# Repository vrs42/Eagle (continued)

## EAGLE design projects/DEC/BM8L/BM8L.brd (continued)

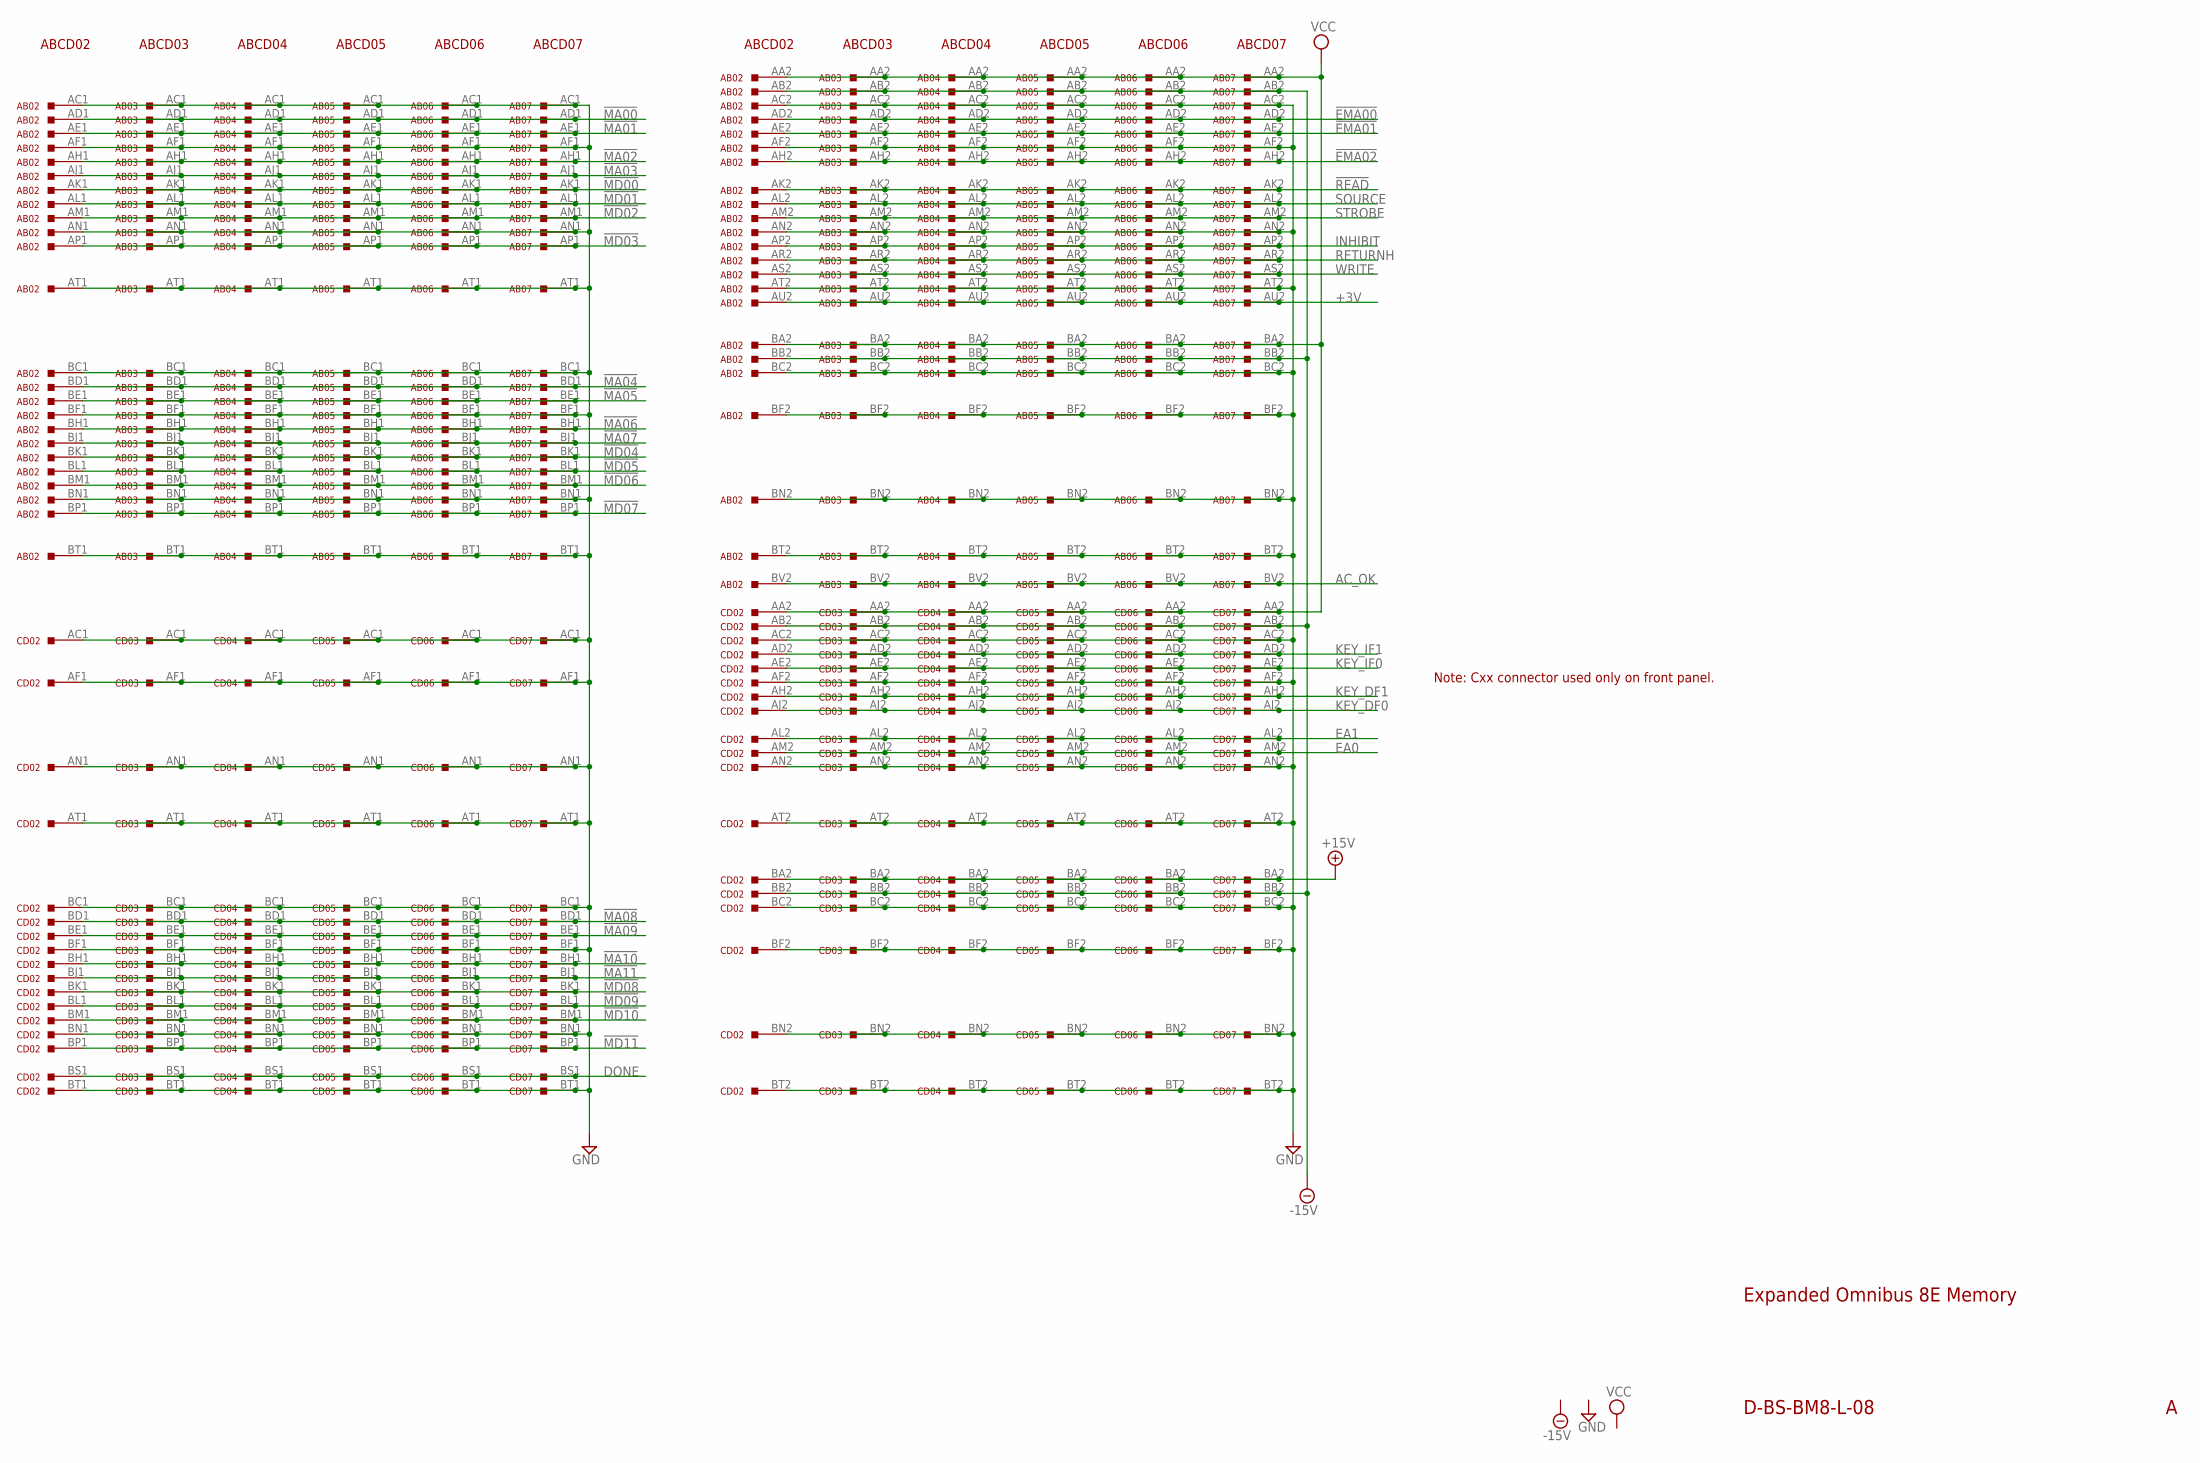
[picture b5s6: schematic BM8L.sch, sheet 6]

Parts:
AB02, AB03, AB04, AB05, AB06: M935; H807-2
AB07: M849; H807-2
CD02, CD03, CD04, CD05, CD06: M935; H807-2
CD07: M849; H807-2

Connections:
!EMA00: AB02.AD2, AB03.AD2, AB04.AD2, AB05.AD2, AB06.AD2, AB07.AD2; also elsewhere on the board
!EMA01: AB02.AE2, AB03.AE2, AB04.AE2, AB05.AE2, AB06.AE2, AB07.AE2; also elsewhere on the board
!EMA02: AB02.AH2, AB03.AH2, AB04.AH2, AB05.AH2, AB06.AH2, AB07.AH2; also elsewhere on the board
!MA00: AB02.AD1, AB03.AD1, AB04.AD1, AB05.AD1, AB06.AD1, AB07.AD1; also elsewhere on the board
!MA01: AB02.AE1, AB03.AE1, AB04.AE1, AB05.AE1, AB06.AE1, AB07.AE1; also elsewhere on the board
!MA02: AB02.AH1, AB03.AH1, AB04.AH1, AB05.AH1, AB06.AH1, AB07.AH1; also elsewhere on the board
!MA03: AB02.AJ1, AB03.AJ1, AB04.AJ1, AB05.AJ1, AB06.AJ1, AB07.AJ1; also elsewhere on the board
!MA04: AB02.BD1, AB03.BD1, AB04.BD1, AB05.BD1, AB06.BD1, AB07.BD1; also elsewhere on the board
!MA05: AB02.BE1, AB03.BE1, AB04.BE1, AB05.BE1, AB06.BE1, AB07.BE1; also elsewhere on the board
!MA06: AB02.BH1, AB03.BH1, AB04.BH1, AB05.BH1, AB06.BH1, AB07.BH1; also elsewhere on the board
!MA07: AB02.BJ1, AB03.BJ1, AB04.BJ1, AB05.BJ1, AB06.BJ1, AB07.BJ1; also elsewhere on the board
!MA08: CD02.BD1, CD03.BD1, CD04.BD1, CD05.BD1, CD06.BD1, CD07.BD1; also elsewhere on the board
!MA09: CD02.BE1, CD03.BE1, CD04.BE1, CD05.BE1, CD06.BE1, CD07.BE1; also elsewhere on the board
!MA10: CD02.BH1, CD03.BH1, CD04.BH1, CD05.BH1, CD06.BH1, CD07.BH1; also elsewhere on the board
!MA11: CD02.BJ1, CD03.BJ1, CD04.BJ1, CD05.BJ1, CD06.BJ1, CD07.BJ1; also elsewhere on the board
!MD00: AB02.AK1, AB03.AK1, AB04.AK1, AB05.AK1, AB06.AK1, AB07.AK1
!MD01: AB02.AL1, AB03.AL1, AB04.AL1, AB05.AL1, AB06.AL1, AB07.AL1
!MD02: AB02.AM1, AB03.AM1, AB04.AM1, AB05.AM1, AB06.AM1, AB07.AM1
!MD03: AB02.AP1, AB03.AP1, AB04.AP1, AB05.AP1, AB06.AP1, AB07.AP1
!MD04: AB02.BK1, AB03.BK1, AB04.BK1, AB05.BK1, AB06.BK1, AB07.BK1
!MD05: AB02.BL1, AB03.BL1, AB04.BL1, AB05.BL1, AB06.BL1, AB07.BL1
!MD06: AB02.BM1, AB03.BM1, AB04.BM1, AB05.BM1, AB06.BM1, AB07.BM1
!MD07: AB02.BP1, AB03.BP1, AB04.BP1, AB05.BP1, AB06.BP1, AB07.BP1
!MD08: CD02.BK1, CD03.BK1, CD04.BK1, CD05.BK1, CD06.BK1, CD07.BK1
!MD09: CD02.BL1, CD03.BL1, CD04.BL1, CD05.BL1, CD06.BL1, CD07.BL1
!MD10: CD02.BM1, CD03.BM1, CD04.BM1, CD05.BM1, CD06.BM1, CD07.BM1
!MD11: CD02.BP1, CD03.BP1, CD04.BP1, CD05.BP1, CD06.BP1, CD07.BP1
!READ: AB02.AK2, AB03.AK2, AB04.AK2, AB05.AK2, AB06.AK2, AB07.AK2; also elsewhere on the board
+3V: AB02.AU2, AB03.AU2, AB04.AU2, AB05.AU2, AB06.AU2, AB07.AU2
+15V: CD02.BA2, CD03.BA2, CD04.BA2, CD05.BA2, CD06.BA2, CD07.BA2
-15V: AB02.AB2, AB02.BB2, AB03.AB2, AB03.BB2, AB04.AB2, AB04.BB2, AB05.AB2, AB05.BB2, AB06.AB2, AB06.BB2, AB07.AB2, AB07.BB2, CD02.AB2, CD02.BB2, CD03.AB2, CD03.BB2, CD04.AB2, CD04.BB2, CD05.AB2, CD05.BB2, CD06.AB2, CD06.BB2, CD07.AB2, CD07.BB2; also elsewhere on the board
AC_OK: AB02.BV2, AB03.BV2, AB04.BV2, AB05.BV2, AB06.BV2, AB07.BV2
DONE: CD02.BS1, CD03.BS1, CD04.BS1, CD05.BS1, CD06.BS1, CD07.BS1; also elsewhere on the board
EA0: CD02.AM2, CD03.AM2, CD04.AM2, CD05.AM2, CD06.AM2, CD07.AM2; also elsewhere on the board
EA1: CD02.AL2, CD03.AL2, CD04.AL2, CD05.AL2, CD06.AL2, CD07.AL2; also elsewhere on the board
GND: AB02.AC1, AB02.AC2, AB02.AF1, AB02.AF2, AB02.AN1, AB02.AN2, AB02.AT1, AB02.AT2, AB02.BC1, AB02.BC2, AB02.BF1, AB02.BF2, AB02.BN1, AB02.BN2, AB02.BT1, AB02.BT2, AB03.AC1, AB03.AC2, AB03.AF1, AB03.AF2, AB03.AN1, AB03.AN2, AB03.AT1, AB03.AT2, AB03.BC1, AB03.BC2, AB03.BF1, AB03.BF2, AB03.BN1, AB03.BN2, AB03.BT1, AB03.BT2, AB04.AC1, AB04.AC2, AB04.AF1, AB04.AF2, AB04.AN1, AB04.AN2, AB04.AT1, AB04.AT2, AB04.BC1, AB04.BC2, AB04.BF1, AB04.BF2, AB04.BN1, AB04.BN2, AB04.BT1, AB04.BT2, AB05.AC1, AB05.AC2, AB05.AF1, AB05.AF2, AB05.AN1, AB05.AN2, AB05.AT1, AB05.AT2, AB05.BC1, AB05.BC2, AB05.BF1, AB05.BF2, AB05.BN1, AB05.BN2, AB05.BT1, AB05.BT2, AB06.AC1, AB06.AC2, AB06.AF1, AB06.AF2, AB06.AN1, AB06.AN2, AB06.AT1, AB06.AT2, AB06.BC1, AB06.BC2, AB06.BF1, AB06.BF2, AB06.BN1, AB06.BN2, AB06.BT1, AB06.BT2, AB07.AC1, AB07.AC2, AB07.AF1, AB07.AF2, AB07.AN1, AB07.AN2, AB07.AT1, AB07.AT2, AB07.BC1, AB07.BC2, AB07.BF1, AB07.BF2, AB07.BN1, AB07.BN2, AB07.BT1, AB07.BT2, CD02.AC1, CD02.AC2, CD02.AF1, CD02.AF2, CD02.AN1, CD02.AN2, CD02.AT1, CD02.AT2, CD02.BC1, CD02.BC2, CD02.BF1, CD02.BF2, CD02.BN1, CD02.BN2, CD02.BT1, CD02.BT2, CD03.AC1, CD03.AC2, CD03.AF1, CD03.AF2, CD03.AN1, CD03.AN2, CD03.AT1, CD03.AT2, CD03.BC1, CD03.BC2, CD03.BF1, CD03.BF2, CD03.BN1, CD03.BN2, CD03.BT1, CD03.BT2, CD04.AC1, CD04.AC2, CD04.AF1, CD04.AF2, CD04.AN1, CD04.AN2, CD04.AT1, CD04.AT2, CD04.BC1, CD04.BC2, CD04.BF1, CD04.BF2, CD04.BN1, CD04.BN2, CD04.BT1, CD04.BT2, CD05.AC1, CD05.AC2, CD05.AF1, CD05.AF2, CD05.AN1, CD05.AN2, CD05.AT1, CD05.AT2, CD05.BC1, CD05.BC2, CD05.BF1, CD05.BF2, CD05.BN1, CD05.BN2, CD05.BT1, CD05.BT2, CD06.AC1, CD06.AC2, CD06.AF1, CD06.AF2, CD06.AN1, CD06.AN2, CD06.AT1, CD06.AT2, CD06.BC1, CD06.BC2, CD06.BF1, CD06.BF2, CD06.BN1, CD06.BN2, CD06.BT1, CD06.BT2, CD07.AC1, CD07.AC2, CD07.AF1, CD07.AF2, CD07.AN1, CD07.AN2, CD07.AT1, CD07.AT2, CD07.BC1, CD07.BC2, CD07.BF1, CD07.BF2, CD07.BN1, CD07.BN2, CD07.BT1, CD07.BT2; also elsewhere on the board
INHIBIT: AB02.AP2, AB03.AP2, AB04.AP2, AB05.AP2, AB06.AP2, AB07.AP2; also elsewhere on the board
KEY_DF0: CD02.AJ2, CD03.AJ2, CD04.AJ2, CD05.AJ2, CD06.AJ2, CD07.AJ2; also elsewhere on the board
KEY_DF1: CD02.AH2, CD03.AH2, CD04.AH2, CD05.AH2, CD06.AH2, CD07.AH2; also elsewhere on the board
KEY_IF0: CD02.AE2, CD03.AE2, CD04.AE2, CD05.AE2, CD06.AE2, CD07.AE2; also elsewhere on the board
KEY_IF1: CD02.AD2, CD03.AD2, CD04.AD2, CD05.AD2, CD06.AD2, CD07.AD2; also elsewhere on the board
RETURNH: AB02.AR2, AB03.AR2, AB04.AR2, AB05.AR2, AB06.AR2, AB07.AR2; also elsewhere on the board
SOURCE: AB02.AL2, AB03.AL2, AB04.AL2, AB05.AL2, AB06.AL2, AB07.AL2; also elsewhere on the board
STROBE: AB02.AM2, AB03.AM2, AB04.AM2, AB05.AM2, AB06.AM2, AB07.AM2; also elsewhere on the board
VCC: AB02.AA2, AB02.BA2, AB03.AA2, AB03.BA2, AB04.AA2, AB04.BA2, AB05.AA2, AB05.BA2, AB06.AA2, AB06.BA2, AB07.AA2, AB07.BA2, CD02.AA2, CD03.AA2, CD04.AA2, CD05.AA2, CD06.AA2, CD07.AA2; also elsewhere on the board
WRITE: AB02.AS2, AB03.AS2, AB04.AS2, AB05.AS2, AB06.AS2, AB07.AS2; also elsewhere on the board

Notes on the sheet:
D-BS-BM8-L-08
Expanded Omnibus 8E Memory
Note: Cxx connector used only on front panel.
ABCD02
ABCD03
ABCD04
ABCD05
ABCD06
ABCD07

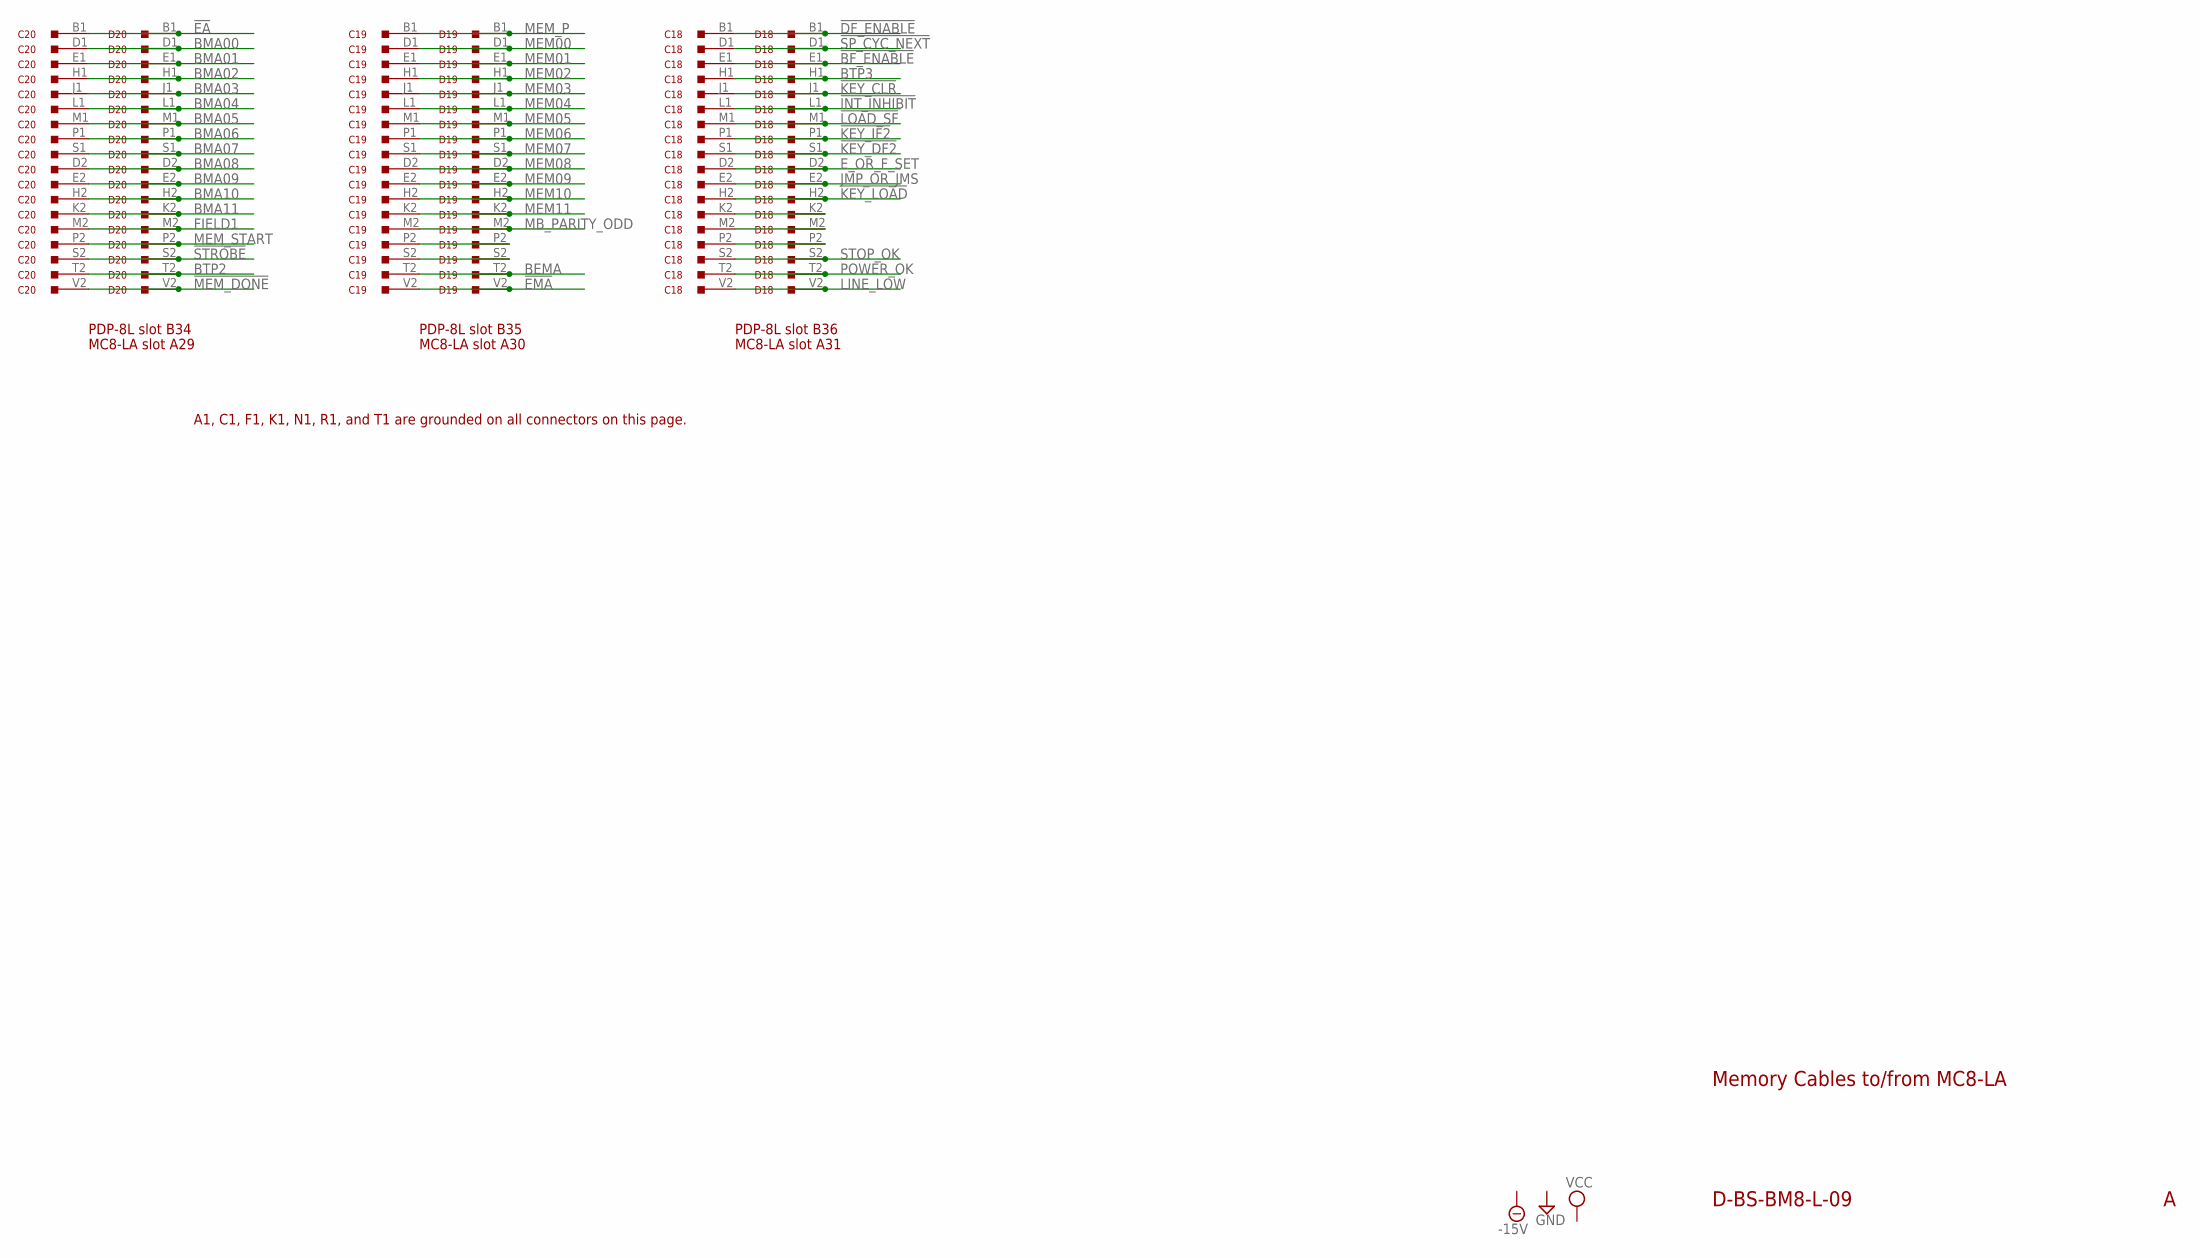
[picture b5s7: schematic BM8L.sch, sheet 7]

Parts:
C18, C19, C20: M903; H807
D18, D19, D20: M903; H807

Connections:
!BF_ENABLE: C18.E1, D18.E1; also elsewhere on the board
!DF_ENABLE: C18.B1, D18.B1; also elsewhere on the board
!EA: C20.B1, D20.B1; also elsewhere on the board
!EMA: C19.V2, D19.V2; also elsewhere on the board
!INT_INHIBIT: C18.L1, D18.L1; also elsewhere on the board
!KEY_CLR: C18.J1, D18.J1; also elsewhere on the board
!KEY_DF2: C18.S1, D18.S1; also elsewhere on the board
!KEY_IF2: C18.P1, D18.P1; also elsewhere on the board
!KEY_LOAD: C18.H2, D18.H2; also elsewhere on the board
!LOAD_SF: C18.M1, D18.M1; also elsewhere on the board
!MEM_DONE: C20.V2, D20.V2; also elsewhere on the board
!SP_CYC_NEXT: C18.D1, D18.D1; also elsewhere on the board
!STROBE: C20.S2, D20.S2; also elsewhere on the board
BEMA: C19.T2, D19.T2; also elsewhere on the board
BMA00: C20.D1, D20.D1; also elsewhere on the board
BMA01: C20.E1, D20.E1; also elsewhere on the board
BMA02: C20.H1, D20.H1; also elsewhere on the board
BMA03: C20.J1, D20.J1; also elsewhere on the board
BMA04: C20.L1, D20.L1; also elsewhere on the board
BMA05: C20.M1, D20.M1; also elsewhere on the board
BMA06: C20.P1, D20.P1; also elsewhere on the board
BMA07: C20.S1, D20.S1; also elsewhere on the board
BMA08: C20.D2, D20.D2; also elsewhere on the board
BMA09: C20.E2, D20.E2; also elsewhere on the board
BMA10: C20.H2, D20.H2; also elsewhere on the board
BMA11: C20.K2, D20.K2; also elsewhere on the board
BTP2: C20.T2, D20.T2; also elsewhere on the board
BTP3: C18.H1, D18.H1; also elsewhere on the board
E_OR_F_SET: C18.D2, D18.D2; also elsewhere on the board
FIELD1: C20.M2, D20.M2; also elsewhere on the board
GND: C18.A1 (GND), C18.C1 (GND), C18.C2 (GND), C18.F1 (GND), C18.F2 (GND), C18.J2 (GND), C18.K1 (GND), C18.L2 (GND), C18.N1 (GND), C18.N2 (GND), C18.R1 (GND), C18.R2 (GND), C18.T1 (GND), C18.U2 (GND), C19.A1 (GND), C19.C1 (GND), C19.C2 (GND), C19.F1 (GND), C19.F2 (GND), C19.J2 (GND), C19.K1 (GND), C19.L2 (GND), C19.N1 (GND), C19.N2 (GND), C19.R1 (GND), C19.R2 (GND), C19.T1 (GND), C19.U2 (GND), C20.A1 (GND), C20.C1 (GND), C20.C2 (GND), C20.F1 (GND), C20.F2 (GND), C20.J2 (GND), C20.K1 (GND), C20.L2 (GND), C20.N1 (GND), C20.N2 (GND), C20.R1 (GND), C20.R2 (GND), C20.T1 (GND), C20.U2 (GND), D18.A1 (GND), D18.C1 (GND), D18.C2 (GND), D18.F1 (GND), D18.F2 (GND), D18.J2 (GND), D18.K1 (GND), D18.L2 (GND), D18.N1 (GND), D18.N2 (GND), D18.R1 (GND), D18.R2 (GND), D18.T1 (GND), D18.U2 (GND), D19.A1 (GND), D19.C1 (GND), D19.C2 (GND), D19.F1 (GND), D19.F2 (GND), D19.J2 (GND), D19.K1 (GND), D19.L2 (GND), D19.N1 (GND), D19.N2 (GND), D19.R1 (GND), D19.R2 (GND), D19.T1 (GND), D19.U2 (GND), D20.A1 (GND), D20.C1 (GND), D20.C2 (GND), D20.F1 (GND), D20.F2 (GND), D20.J2 (GND), D20.K1 (GND), D20.L2 (GND), D20.N1 (GND), D20.N2 (GND), D20.R1 (GND), D20.R2 (GND), D20.T1 (GND), D20.U2 (GND); also elsewhere on the board
JMP_OR_JMS: C18.E2, D18.E2; also elsewhere on the board
LINE_LOW: C18.V2, D18.V2
MB_PARITY_ODD: C19.M2, D19.M2
MEM00: C19.D1, D19.D1; also elsewhere on the board
MEM01: C19.E1, D19.E1; also elsewhere on the board
MEM02: C19.H1, D19.H1; also elsewhere on the board
MEM03: C19.J1, D19.J1; also elsewhere on the board
MEM04: C19.L1, D19.L1; also elsewhere on the board
MEM05: C19.M1, D19.M1; also elsewhere on the board
MEM06: C19.P1, D19.P1; also elsewhere on the board
MEM07: C19.S1, D19.S1; also elsewhere on the board
MEM08: C19.D2, D19.D2; also elsewhere on the board
MEM09: C19.E2, D19.E2; also elsewhere on the board
MEM10: C19.H2, D19.H2; also elsewhere on the board
MEM11: C19.K2, D19.K2; also elsewhere on the board
MEM_P: C19.B1, D19.B1
MEM_START: C20.P2, D20.P2; also elsewhere on the board
unnamed: C19.P2, D19.P2
unnamed: C19.S2, D19.S2
unnamed: C18.P2, D18.P2
unnamed: C18.M2, D18.M2
unnamed: C18.K2, D18.K2
POWER_OK: C18.T2, D18.T2; also elsewhere on the board
STOP_OK: C18.S2, D18.S2

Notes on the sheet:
D-BS-BM8-L-09
Memory Cables to/from MC8-LA
A1, C1, F1, K1, N1, R1, and T1 are grounded on all connectors on this page.
PDP-8L slot B34
MC8-LA slot A29
PDP-8L slot B35
MC8-LA slot A30
PDP-8L slot B36
MC8-LA slot A31

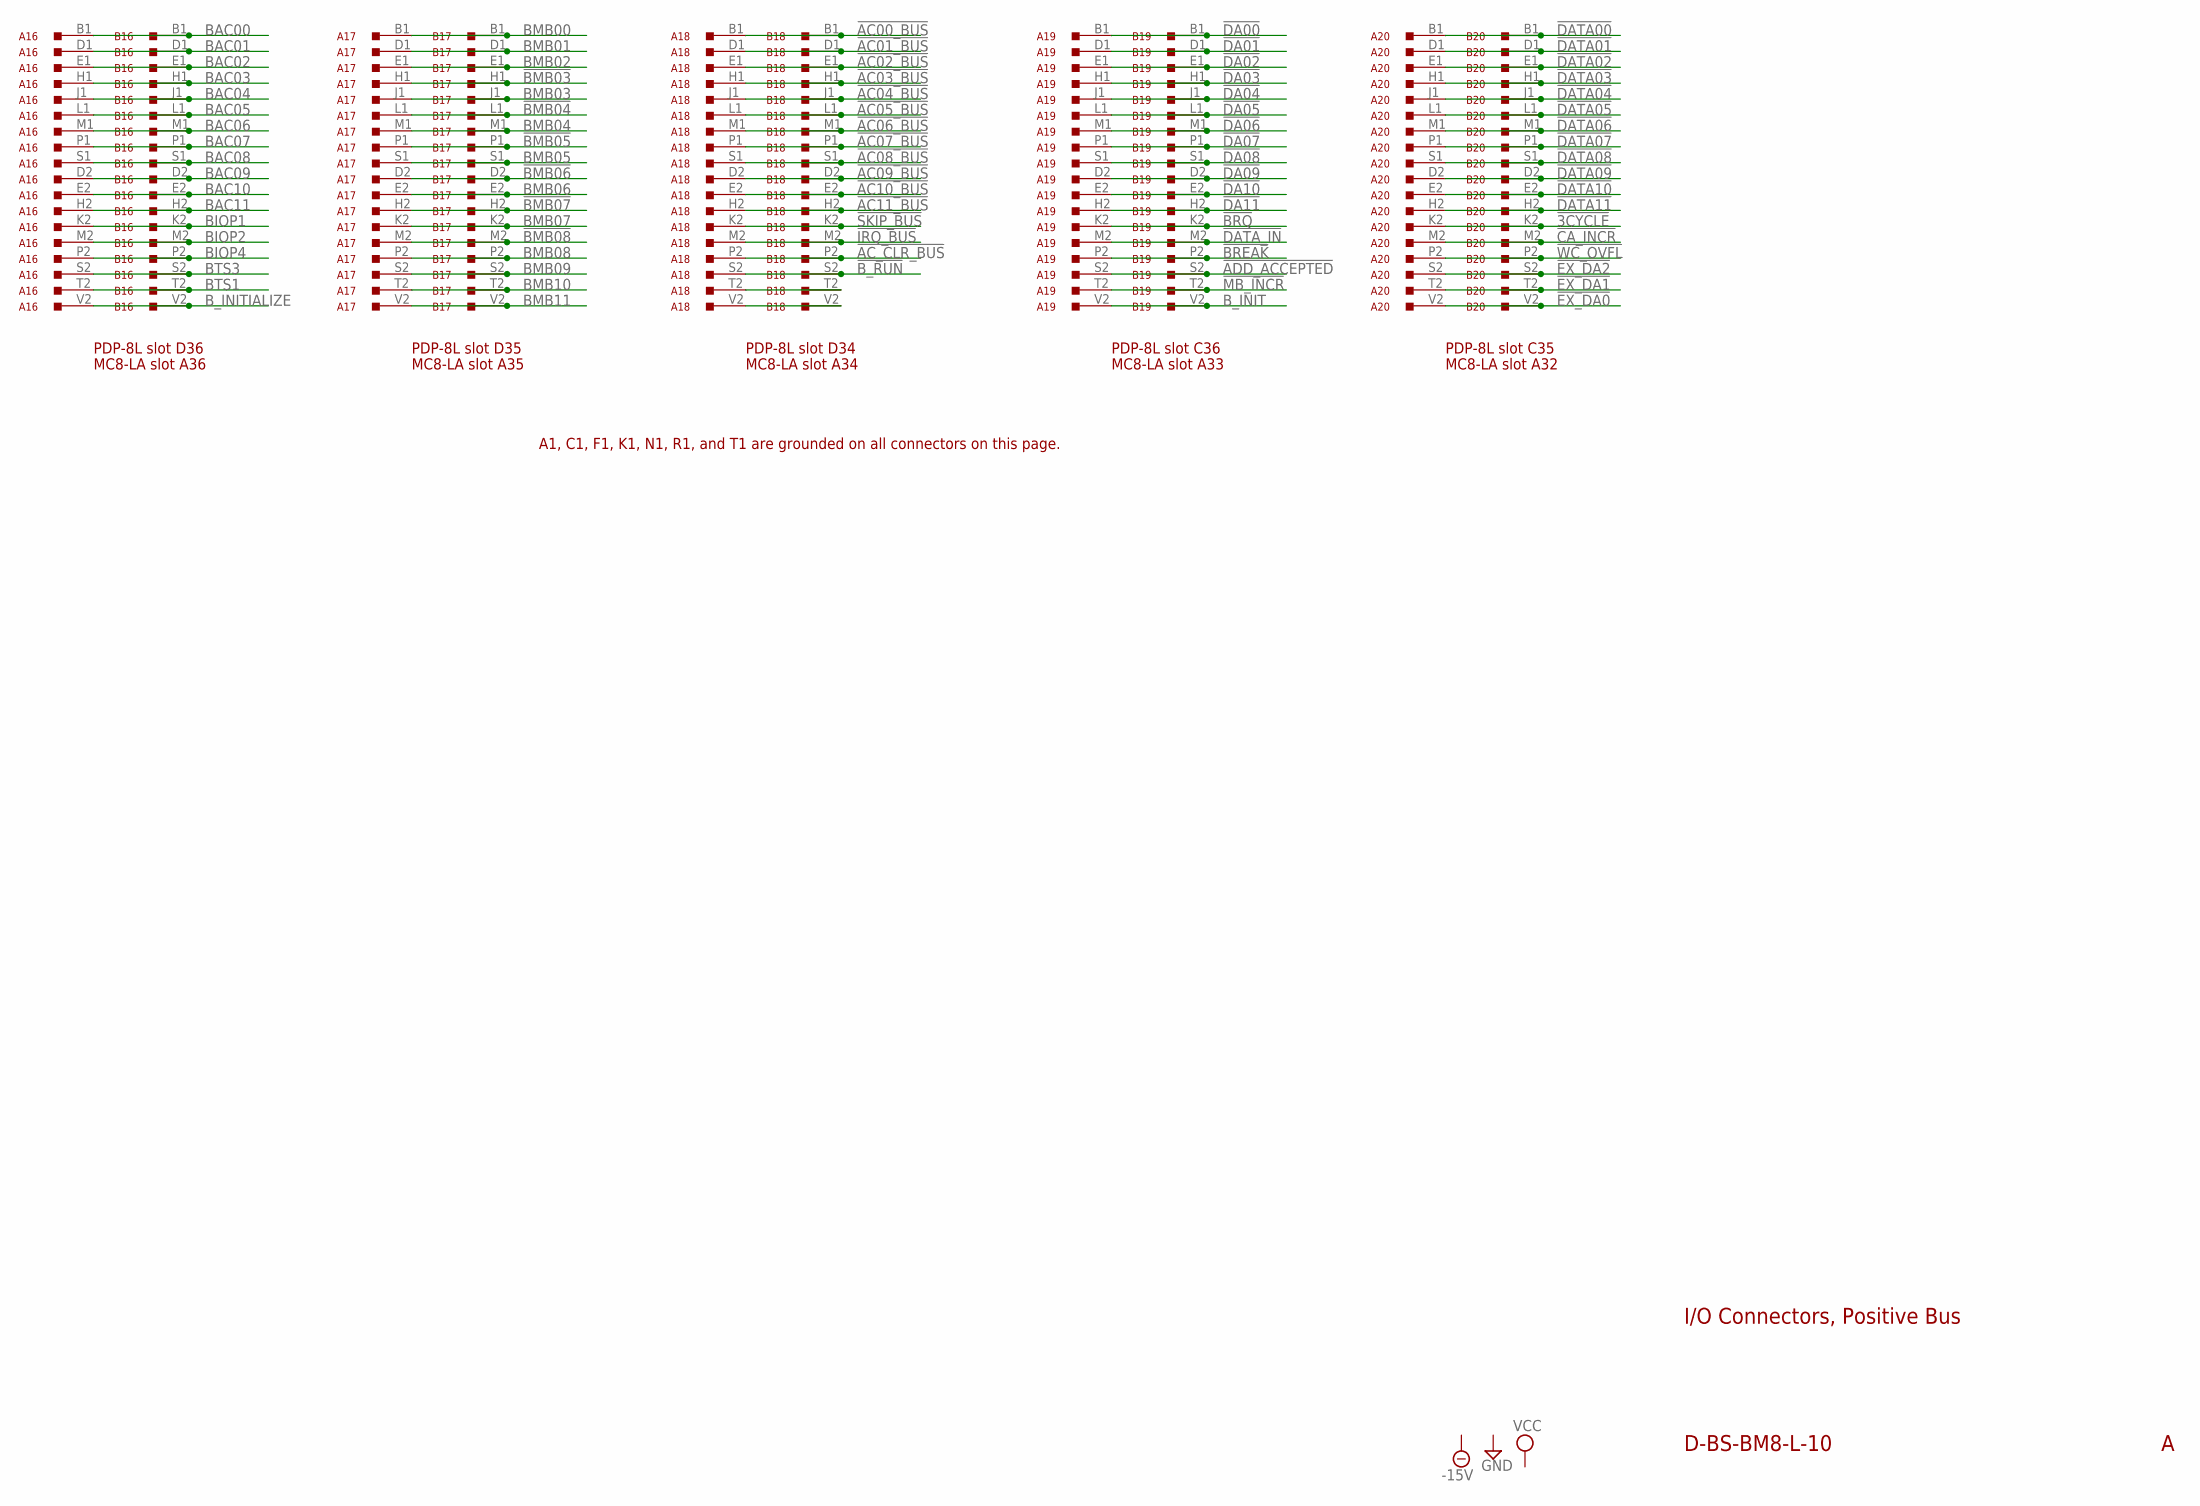
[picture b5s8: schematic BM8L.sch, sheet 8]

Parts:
A16, A17, A18, A19, A20: M903; H807
B16, B17, B18, B19, B20: M903; H807

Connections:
!3CYCLE: A20.K2, B20.K2
!AC00_BUS: A18.B1, B18.B1
!AC01_BUS: A18.D1, B18.D1
!AC02_BUS: A18.E1, B18.E1
!AC03_BUS: A18.H1, B18.H1
!AC04_BUS: A18.J1, B18.J1
!AC05_BUS: A18.L1, B18.L1
!AC06_BUS: A18.M1, B18.M1; also elsewhere on the board
!AC07_BUS: A18.P1, B18.P1; also elsewhere on the board
!AC08_BUS: A18.S1, B18.S1; also elsewhere on the board
!AC09_BUS: A18.D2, B18.D2; also elsewhere on the board
!AC10_BUS: A18.E2, B18.E2; also elsewhere on the board
!AC11_BUS: A18.H2, B18.H2; also elsewhere on the board
!AC_CLR_BUS: A18.P2, B18.P2
!ADD_ACCEPTED: A19.S2, B19.S2
!BMB03: A17.H1, B17.H1; also elsewhere on the board
!BMB04: A17.L1, B17.L1; also elsewhere on the board
!BMB05: A17.P1, B17.P1; also elsewhere on the board
!BMB06: A17.D2, B17.D2; also elsewhere on the board
!BMB07: A17.H2, B17.H2; also elsewhere on the board
!BMB08: A17.M2, B17.M2; also elsewhere on the board
!BREAK: A19.P2, B19.P2
!BRQ: A19.K2, B19.K2
!B_RUN: A18.S2, B18.S2
!CA_INCR: A20.M2, B20.M2
!DA00: A19.B1, B19.B1
!DA01: A19.D1, B19.D1
!DA02: A19.E1, B19.E1
!DA03: A19.H1, B19.H1
!DA04: A19.J1, B19.J1
!DA05: A19.L1, B19.L1
!DA06: A19.M1, B19.M1
!DA07: A19.P1, B19.P1
!DA08: A19.S1, B19.S1
!DA09: A19.D2, B19.D2
!DA10: A19.E2, B19.E2
!DA11: A19.H2, B19.H2
!DATA00: A20.B1, B20.B1
!DATA01: A20.D1, B20.D1
!DATA02: A20.E1, B20.E1
!DATA03: A20.H1, B20.H1
!DATA04: A20.J1, B20.J1
!DATA05: A20.L1, B20.L1
!DATA06: A20.M1, B20.M1
!DATA07: A20.P1, B20.P1
!DATA08: A20.S1, B20.S1
!DATA09: A20.D2, B20.D2
!DATA10: A20.E2, B20.E2
!DATA11: A20.H2, B20.H2
!DATA_IN: A19.M2, B19.M2
!EX_DA0: A20.V2, B20.V2; also elsewhere on the board
!EX_DA1: A20.T2, B20.T2; also elsewhere on the board
!EX_DA2: A20.S2, B20.S2; also elsewhere on the board
!IRQ_BUS: A18.M2, B18.M2
!MB_INCR: A19.T2, B19.T2
!SKIP_BUS: A18.K2, B18.K2
!WC_OVFL: A20.P2, B20.P2
BAC00: A16.B1, B16.B1
BAC01: A16.D1, B16.D1
BAC02: A16.E1, B16.E1
BAC03: A16.H1, B16.H1
BAC04: A16.J1, B16.J1
BAC05: A16.L1, B16.L1
BAC06: A16.M1, B16.M1
BAC07: A16.P1, B16.P1
BAC08: A16.S1, B16.S1
BAC09: A16.D2, B16.D2
BAC10: A16.E2, B16.E2
BAC11: A16.H2, B16.H2
BIOP1: A16.K2, B16.K2; also elsewhere on the board
BIOP2: A16.M2, B16.M2; also elsewhere on the board
BIOP4: A16.P2, B16.P2; also elsewhere on the board
BMB00: A17.B1, B17.B1; also elsewhere on the board
BMB01: A17.D1, B17.D1; also elsewhere on the board
BMB02: A17.E1, B17.E1; also elsewhere on the board
BMB03: A17.J1, B17.J1; also elsewhere on the board
BMB04: A17.M1, B17.M1; also elsewhere on the board
BMB05: A17.S1, B17.S1; also elsewhere on the board
BMB06: A17.E2, B17.E2; also elsewhere on the board
BMB07: A17.K2, B17.K2; also elsewhere on the board
BMB08: A17.P2, B17.P2; also elsewhere on the board
BMB09: A17.S2, B17.S2; also elsewhere on the board
BMB10: A17.T2, B17.T2; also elsewhere on the board
BMB11: A17.V2, B17.V2; also elsewhere on the board
BTS1: A16.T2, B16.T2
BTS3: A16.S2, B16.S2
B_INIT: A19.V2, B19.V2; also elsewhere on the board
B_INITIALIZE: A16.V2, B16.V2
GND: A16.A1 (GND), A16.C1 (GND), A16.C2 (GND), A16.F1 (GND), A16.F2 (GND), A16.J2 (GND), A16.K1 (GND), A16.L2 (GND), A16.N1 (GND), A16.N2 (GND), A16.R1 (GND), A16.R2 (GND), A16.T1 (GND), A16.U2 (GND), A17.A1 (GND), A17.C1 (GND), A17.C2 (GND), A17.F1 (GND), A17.F2 (GND), A17.J2 (GND), A17.K1 (GND), A17.L2 (GND), A17.N1 (GND), A17.N2 (GND), A17.R1 (GND), A17.R2 (GND), A17.T1 (GND), A17.U2 (GND), A18.A1 (GND), A18.C1 (GND), A18.C2 (GND), A18.F1 (GND), A18.F2 (GND), A18.J2 (GND), A18.K1 (GND), A18.L2 (GND), A18.N1 (GND), A18.N2 (GND), A18.R1 (GND), A18.R2 (GND), A18.T1 (GND), A18.U2 (GND), A19.A1 (GND), A19.C1 (GND), A19.C2 (GND), A19.F1 (GND), A19.F2 (GND), A19.J2 (GND), A19.K1 (GND), A19.L2 (GND), A19.N1 (GND), A19.N2 (GND), A19.R1 (GND), A19.R2 (GND), A19.T1 (GND), A19.U2 (GND), A20.A1 (GND), A20.C1 (GND), A20.C2 (GND), A20.F1 (GND), A20.F2 (GND), A20.J2 (GND), A20.K1 (GND), A20.L2 (GND), A20.N1 (GND), A20.N2 (GND), A20.R1 (GND), A20.R2 (GND), A20.T1 (GND), A20.U2 (GND), B16.A1 (GND), B16.C1 (GND), B16.C2 (GND), B16.F1 (GND), B16.F2 (GND), B16.J2 (GND), B16.K1 (GND), B16.L2 (GND), B16.N1 (GND), B16.N2 (GND), B16.R1 (GND), B16.R2 (GND), B16.T1 (GND), B16.U2 (GND), B17.A1 (GND), B17.C1 (GND), B17.C2 (GND), B17.F1 (GND), B17.F2 (GND), B17.J2 (GND), B17.K1 (GND), B17.L2 (GND), B17.N1 (GND), B17.N2 (GND), B17.R1 (GND), B17.R2 (GND), B17.T1 (GND), B17.U2 (GND), B18.A1 (GND), B18.C1 (GND), B18.C2 (GND), B18.F1 (GND), B18.F2 (GND), B18.J2 (GND), B18.K1 (GND), B18.L2 (GND), B18.N1 (GND), B18.N2 (GND), B18.R1 (GND), B18.R2 (GND), B18.T1 (GND), B18.U2 (GND), B19.A1 (GND), B19.C1 (GND), B19.C2 (GND), B19.F1 (GND), B19.F2 (GND), B19.J2 (GND), B19.K1 (GND), B19.L2 (GND), B19.N1 (GND), B19.N2 (GND), B19.R1 (GND), B19.R2 (GND), B19.T1 (GND), B19.U2 (GND), B20.A1 (GND), B20.C1 (GND), B20.C2 (GND), B20.F1 (GND), B20.F2 (GND), B20.J2 (GND), B20.K1 (GND), B20.L2 (GND), B20.N1 (GND), B20.N2 (GND), B20.R1 (GND), B20.R2 (GND), B20.T1 (GND), B20.U2 (GND); also elsewhere on the board
unnamed: A18.V2, B18.V2
unnamed: A18.T2, B18.T2

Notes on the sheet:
D-BS-BM8-L-10
I/O Connectors, Positive Bus
A1, C1, F1, K1, N1, R1, and T1 are grounded on all connectors on this page.
PDP-8L slot D36
MC8-LA slot A36
PDP-8L slot D35
MC8-LA slot A35
PDP-8L slot D34
MC8-LA slot A34
PDP-8L slot C36
MC8-LA slot A33
PDP-8L slot C35
MC8-LA slot A32

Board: 2 copper layers, 66 parts (0 on the bottom side), 389 nets, no tracks yet.
